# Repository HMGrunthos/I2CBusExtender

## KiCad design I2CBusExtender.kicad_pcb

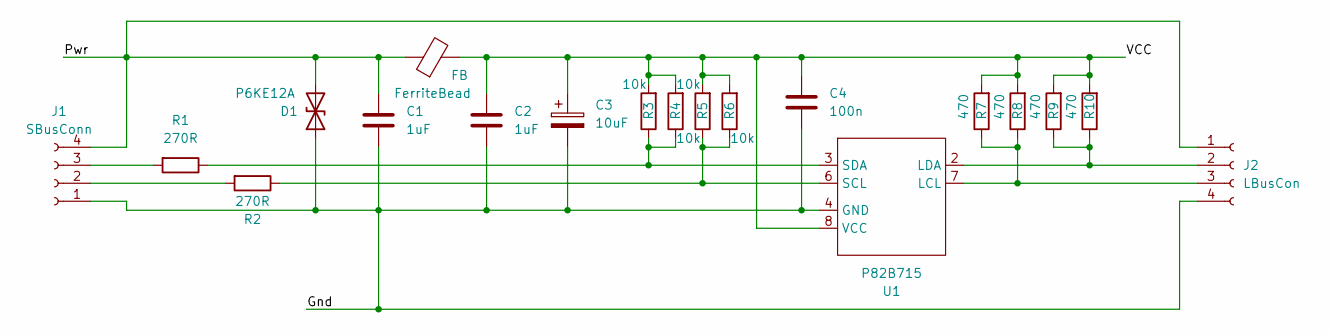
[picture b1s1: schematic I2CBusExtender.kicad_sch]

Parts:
C1, C2: 1uF; C_1206_3216Metric_Pad1.33x1.80mm_HandSolder
C3: 10uF; CP_Radial_D5.0mm_P2.00mm
C4: 100n; C_1206_3216Metric_Pad1.33x1.80mm_HandSolder
D1: P6KE12A; D_DO-15_P12.70mm_Horizontal
FB: FerriteBead; EXCEL_DR35C
J1: SBusConn; SolderWire-0.5sqmm_1x04_P4.6mm_D0.9mm_OD2.1mm_Relief
J2: LBusCon; SolderWire-0.5sqmm_1x04_P4.6mm_D0.9mm_OD2.1mm_Relief
R1, R2: 270R; R_Axial_DIN0207_L6.3mm_D2.5mm_P7.62mm_Horizontal
R3, R5: 10k; R_Axial_DIN0207_L6.3mm_D2.5mm_P5.08mm_Vertical
R4, R6: 10k; R_1206_3216Metric_Pad1.30x1.75mm_HandSolder
R7, R9: 470; R_1206_3216Metric_Pad1.30x1.75mm_HandSolder
R8, R10: 470; R_Axial_DIN0207_L6.3mm_D2.5mm_P5.08mm_Vertical
U1: P82B715; SO-8_3.9x4.9mm_P1.27mm

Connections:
/Gnd: C1.2, C2.2, C3.2, C4.2, D1.1 (A1), J1.1, J2.4, U1.4 (GND)
/Pwr: C1.1, D1.2 (A2), FB.1, J1.4, J2.1
/VCC: C2.1, C3.1, C4.1, FB.2, R3.2, R4.2, R5.2, R6.2, R7.2, R8.2, R9.2, R10.2, U1.8 (VCC)
unnamed: J1.2, R2.2
unnamed: J1.3, R1.2
unnamed: J2.2, R9.1, R10.1, U1.2 (LDA)
unnamed: J2.3, R7.1, R8.1, U1.7 (LCL)
unnamed: R1.1, R3.1, R4.1, U1.3 (SDA)
unnamed: R2.1, R5.1, R6.1, U1.6 (SCL)

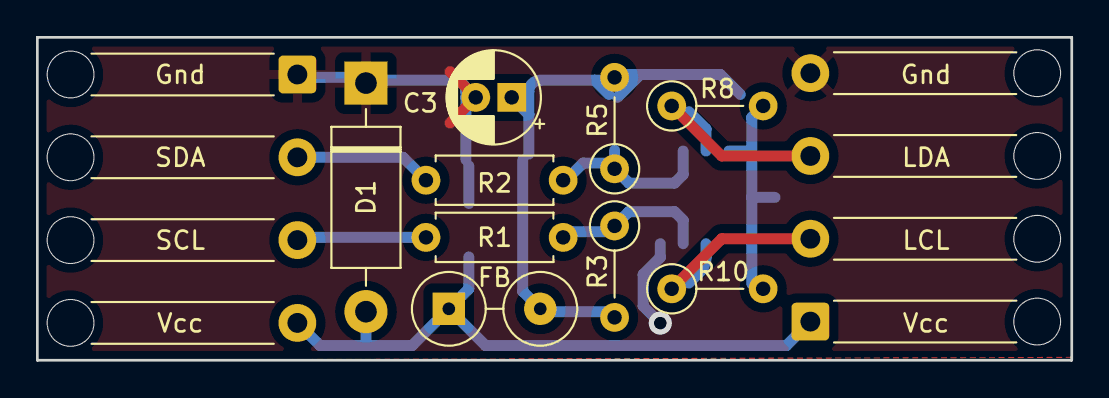
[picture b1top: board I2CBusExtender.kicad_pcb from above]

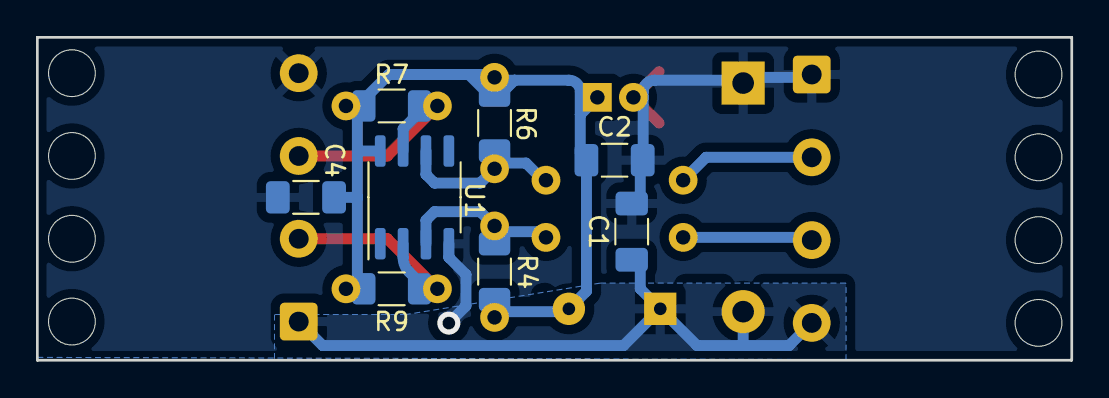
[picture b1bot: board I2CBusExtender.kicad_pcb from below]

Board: 2 copper layers, 57.5 x 17.9 mm, 19 parts (8 on the bottom side), 9 nets.

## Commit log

2022-12-07 Initial schematic.
2022-12-07 Initial layout and footprint adjustment complete.
2022-12-08 Tweaked schematic layout and improved board design to the point it passes DRC.
2022-12-09 Tweaked layouts and footprints.
2022-12-09 Tidied up track layout to make track rounding and filleting work better.
2022-12-09 Renamed some nets.
2022-12-09 Added silk screen pad labels and tidied up a track.
2022-12-14 Added ferrite bead footprint.
2022-12-15 Added new ferrite bead footprint to PCB.
2022-12-15 Tweaked spaces between components and improved track layout.
2022-12-15 Tweaked track layout.
2022-12-15 Simplified some tracks.
2022-12-16 Fixed footprint in schematic.
2023-01-22 Added teardrops to board front GND plane.
